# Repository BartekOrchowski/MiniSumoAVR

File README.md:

## MiniSumo Robot – ATmega328P 

This project is a MiniSumo robot developed during a workshop organized by the KoNaR student scientific association. It is based on the ATmega328P microcontroller and represents my first hands-on experience with designing, assembling, and programming a robot from scratch.

## Overview

The goal of the project was to create an autonomous MiniSumo robot that could:
- Detect and engage with an opponent using distance sensors
- Stay within the ring using line sensors
- Control DC motors for movement via an H-bridge

## Working Features

Despite the project being incomplete, several features were successfully implemented:
- ✅ **DC motor control** using an H-bridge
- ✅ **Distance measurement** from four VL53L0X sensors (basic functionality working)
- ✅ **ADC** for line sensor

## Issues and Challenges

Several hardware issues:
- ❌ Incorrect electrical connections
- ❌ Improper wiring of XSHUT pins for the VL53L0X distance sensors

Due to these problems, the robot was not fully operational, and the project was paused before final testing and competition.

## Future Plans

Although the current version of the robot is unfinished, I may return to this project in the future to redesign the PCB, correct the hardware issues, and complete the software stack.

---

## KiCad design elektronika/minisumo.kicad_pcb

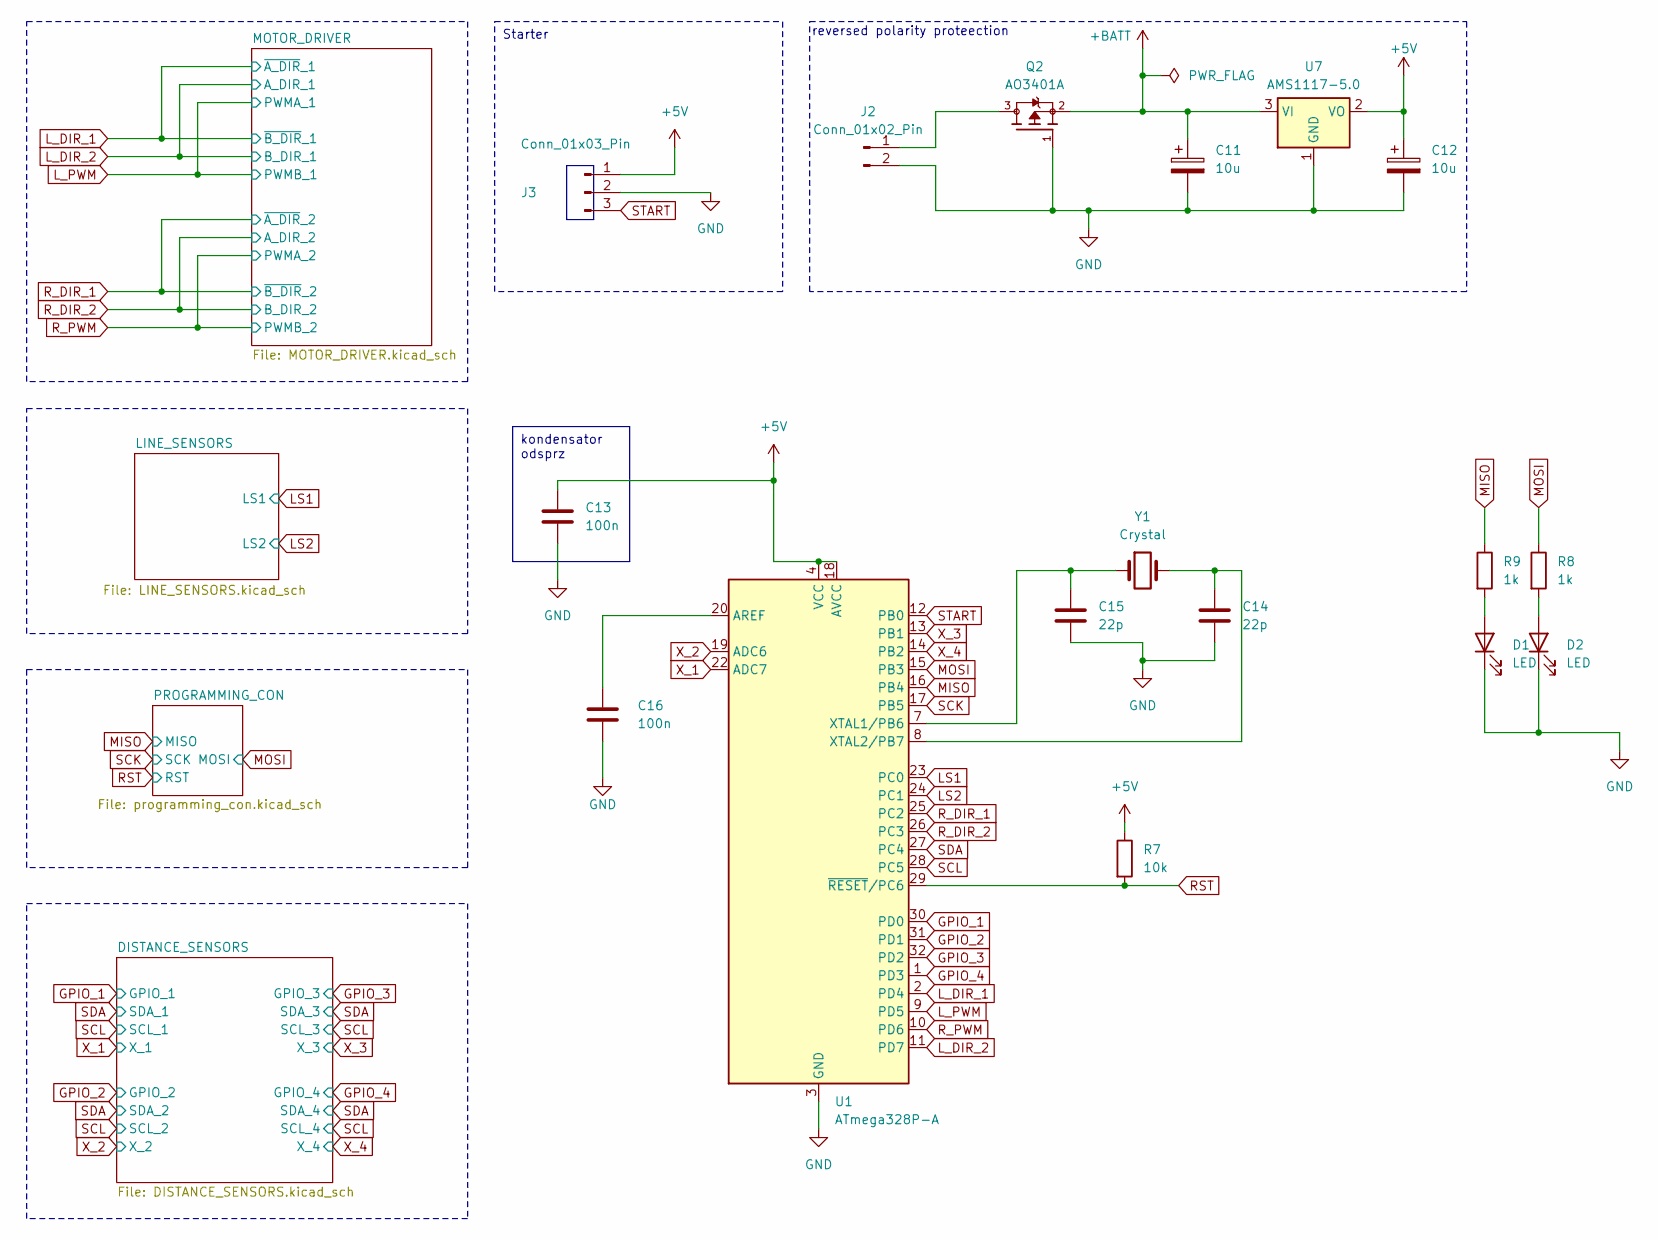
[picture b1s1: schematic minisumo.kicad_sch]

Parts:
C11, C12: 10u; CP_EIA-3528-21_Kemet-B_Pad1.50x2.35mm_HandSolder
C13, C16: 100n; LED_0805_2012Metric_Pad1.15x1.40mm_HandSolder
C14, C15: 22p; LED_0805_2012Metric_Pad1.15x1.40mm_HandSolder
D1, D2: LED; LED_0805_2012Metric_Pad1.15x1.40mm_HandSolder
J2: Conn_01x02_Pin; PinHeader_1x02_P2.54mm_Vertical
J3: Conn_01x03_Pin; PinHeader_1x03_P2.54mm_Vertical
Q2: AO3401A; SOT23-3; DigiKey_Part_Number 785-1001-2-ND
R7: 10k; R_0805_2012Metric_Pad1.20x1.40mm_HandSolder
R8, R9: 1k; R_0805_2012Metric_Pad1.20x1.40mm_HandSolder
U1: ATmega328P-A; TQFP-32_7x7mm_P0.8mm
U7: AMS1117-5.0; SOT-223-3_TabPin2
Y1: Crystal; Crystal_HC18-U_Vertical

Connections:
+5V: C12.1, C13.1, J3.1, R7.1, U1.4 (VCC), U1.6 (VCC), U1.18 (AVCC), U7.2 (VO); also elsewhere on the board
+BATT: C11.1, Q2.2, U7.3 (VI); also elsewhere on the board
GND: C11.2, C12.2, C13.2, C14.2, C15.2, C16.2, D1.1 (K), D2.1 (K), J2.2, J3.2, Q2.1, U1.3 (GND), U1.5 (GND), U1.21 (GND), U7.1 (GND); also elsewhere on the board
GPIO_1: U1.30 (PD0); also elsewhere on the board
GPIO_2: U1.31 (PD1); also elsewhere on the board
GPIO_3: U1.32 (PD2); also elsewhere on the board
GPIO_4: U1.1 (PD3); also elsewhere on the board
LS1: U1.23 (PC0); also elsewhere on the board
LS2: U1.24 (PC1); also elsewhere on the board
L_DIR_1: U1.2 (PD4); also elsewhere on the board
L_DIR_2: U1.11 (PD7); also elsewhere on the board
L_PWM: U1.9 (PD5); also elsewhere on the board
MISO: R9.1, U1.16 (PB4); also elsewhere on the board
MOSI: R8.1, U1.15 (PB3); also elsewhere on the board
unnamed: D1.2 (A), R9.2
unnamed: D2.2 (A), R8.2
unnamed: J2.1, Q2.3
unnamed: C16.1, U1.20 (AREF)
unnamed: C15.1, U1.7 (XTAL1/PB6), Y1.1
unnamed: C14.1, U1.8 (XTAL2/PB7), Y1.2
RST: R7.2, U1.29 (~RESET/PC6); also elsewhere on the board
R_DIR_1: U1.25 (PC2); also elsewhere on the board
R_DIR_2: U1.26 (PC3); also elsewhere on the board
R_PWM: U1.10 (PD6); also elsewhere on the board
SCK: U1.17 (PB5); also elsewhere on the board
SCL: U1.28 (PC5); also elsewhere on the board
SDA: U1.27 (PC4); also elsewhere on the board
START: J3.3, U1.12 (PB0)
X_1: U1.22 (ADC7); also elsewhere on the board
X_2: U1.19 (ADC6); also elsewhere on the board
X_3: U1.13 (PB1); also elsewhere on the board
X_4: U1.14 (PB2); also elsewhere on the board

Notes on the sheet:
kondensator odsprz
Starter
reversed polarity proteection

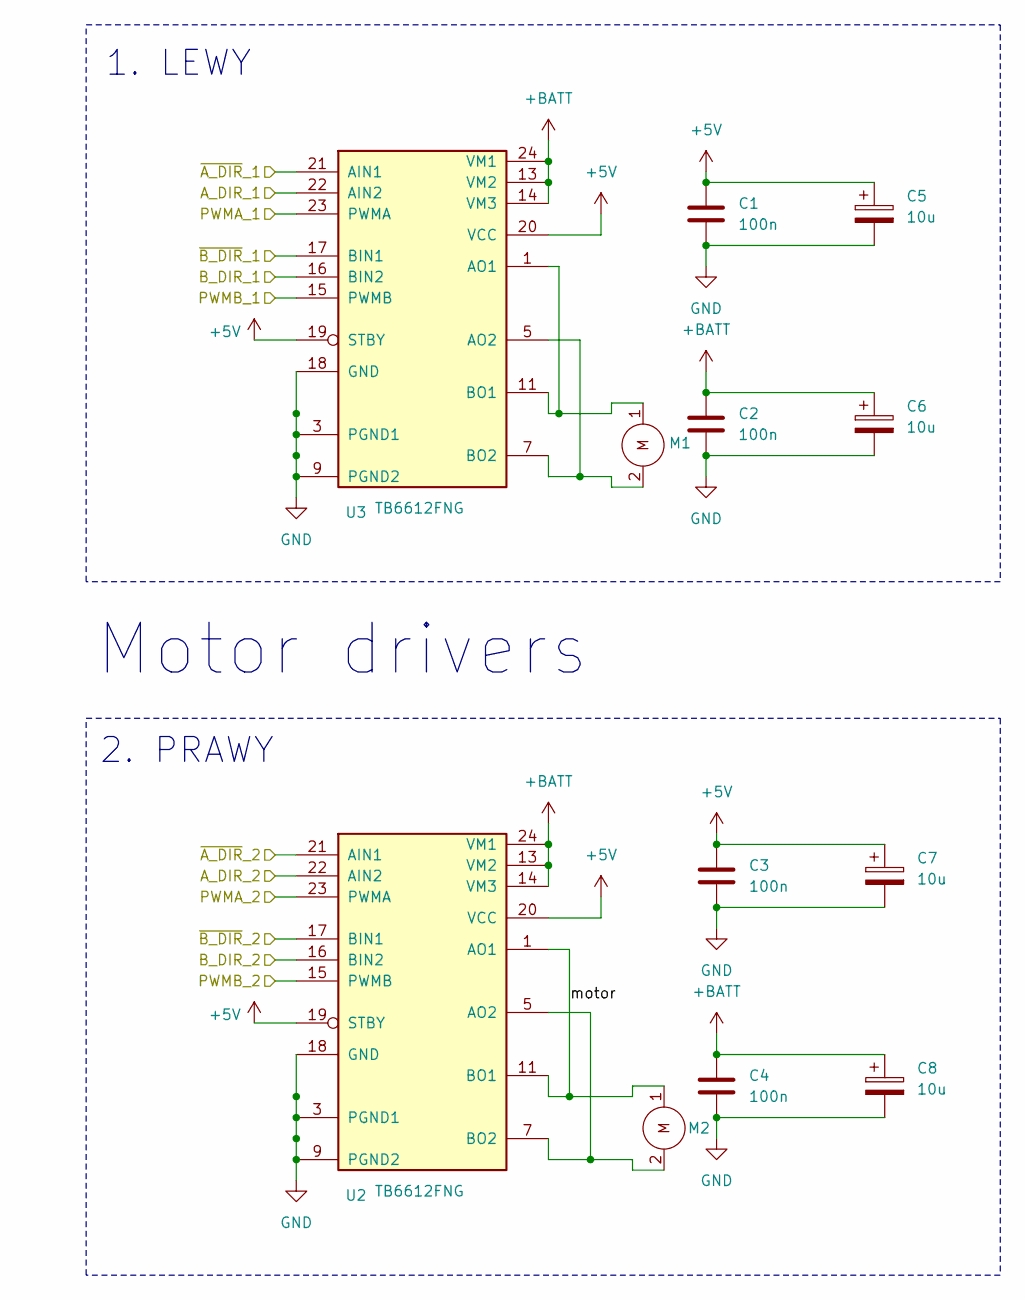
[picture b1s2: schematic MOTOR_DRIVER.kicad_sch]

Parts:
C1, C2, C3, C4: 100n; LED_0805_2012Metric_Pad1.15x1.40mm_HandSolder
C5, C6, C7, C8: 10u; CP_EIA-3528-21_Kemet-B_Pad1.50x2.35mm_HandSolder
M1, M2: Motor
U2, U3: TB6612FNG; SSOP-24_5.3x8.2mm_P0.65mm

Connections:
+5V: C1.1, C3.1, C5.1, C7.1, U2.19 (STBY), U2.20 (VCC), U3.19 (STBY), U3.20 (VCC); also elsewhere on the board
+BATT: C2.1, C4.1, C6.1, C8.1, U2.13 (VM2), U2.14 (VM3), U2.24 (VM1), U3.13 (VM2), U3.14 (VM3), U3.24 (VM1); also elsewhere on the board
/MOTOR_DRIVER/motor: M2.1, U2.1 (AO1), U2.2 (AO1), U2.11 (BO1), U2.12 (BO1)
GND: C1.2, C2.2, C3.2, C4.2, C5.2, C6.2, C7.2, C8.2, U2.3 (PGND1), U2.4 (PGND1), U2.9 (PGND2), U2.10 (PGND2), U2.18 (GND), U3.3 (PGND1), U3.4 (PGND1), U3.9 (PGND2), U3.10 (PGND2), U3.18 (GND); also elsewhere on the board
L_DIR_1: U3.17 (BIN1), U3.21 (AIN1); also elsewhere on the board
L_DIR_2: U3.16 (BIN2), U3.22 (AIN2); also elsewhere on the board
L_PWM: U3.15 (PWMB), U3.23 (PWMA); also elsewhere on the board
unnamed: M1.1, U3.1 (AO1), U3.2 (AO1), U3.11 (BO1), U3.12 (BO1)
unnamed: M1.2, U3.5 (AO2), U3.6 (AO2), U3.7 (BO2), U3.8 (BO2)
unnamed: M2.2, U2.5 (AO2), U2.6 (AO2), U2.7 (BO2), U2.8 (BO2)
R_DIR_1: U2.17 (BIN1), U2.21 (AIN1); also elsewhere on the board
R_DIR_2: U2.16 (BIN2), U2.22 (AIN2); also elsewhere on the board
R_PWM: U2.15 (PWMB), U2.23 (PWMA); also elsewhere on the board

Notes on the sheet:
1. LEWY
2. PRAWY
Motor drivers

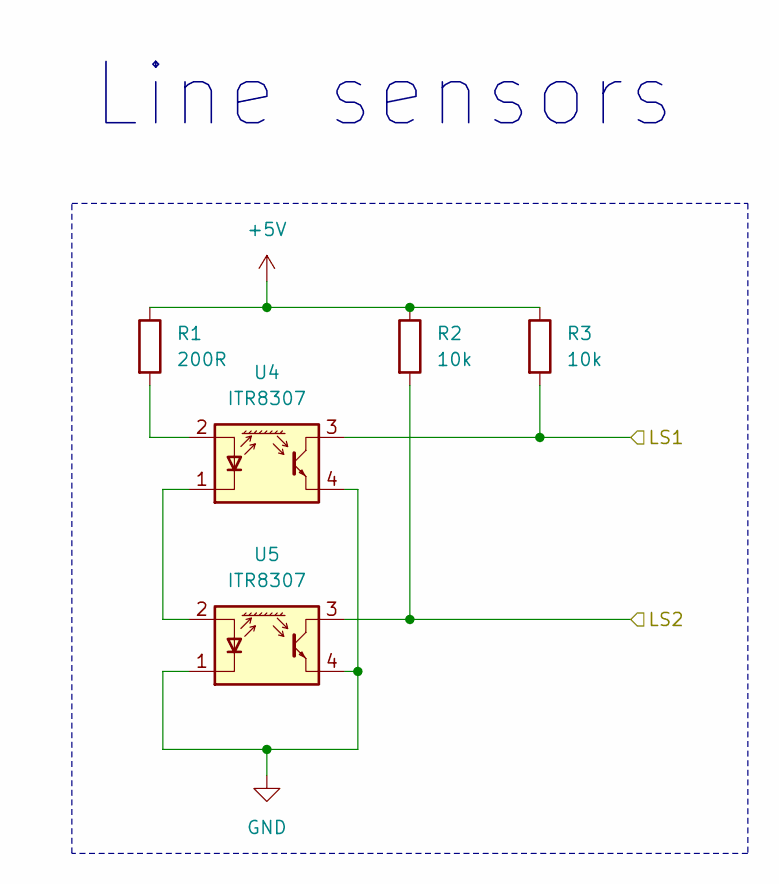
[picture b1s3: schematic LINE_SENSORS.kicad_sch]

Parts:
R1: 200R; R_0805_2012Metric_Pad1.20x1.40mm_HandSolder
R2, R3: 10k; R_0805_2012Metric_Pad1.20x1.40mm_HandSolder
U4, U5: ITR8307; Everlight_ITR1201SR10AR

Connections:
+5V: R1.1, R2.1, R3.1; also elsewhere on the board
GND: U4.4 (E), U5.1 (K), U5.4 (E); also elsewhere on the board
LS1: R3.2, U4.3 (C); also elsewhere on the board
LS2: R2.2, U5.3 (C); also elsewhere on the board
unnamed: R1.2, U4.2 (A)
unnamed: U4.1 (K), U5.2 (A)

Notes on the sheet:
Line sensors

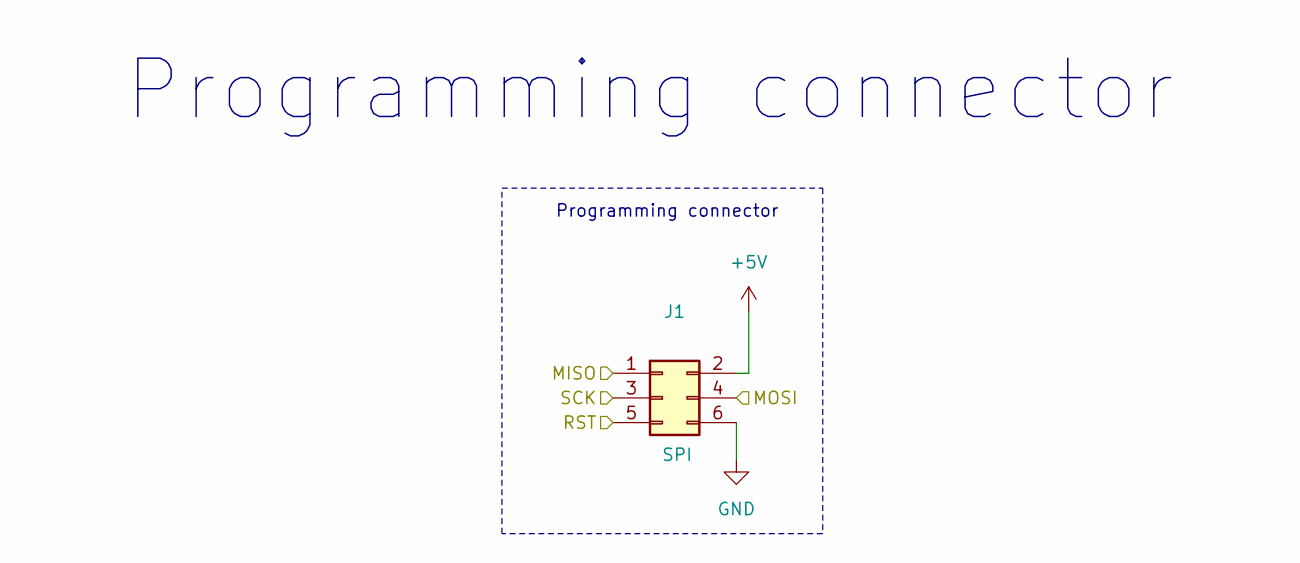
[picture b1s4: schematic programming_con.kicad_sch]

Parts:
J1: SPI; PinHeader_2x03_P2.54mm_Vertical

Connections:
+5V: J1.2; also elsewhere on the board
GND: J1.6; also elsewhere on the board
MISO: J1.1; also elsewhere on the board
MOSI: J1.4; also elsewhere on the board
RST: J1.5; also elsewhere on the board
SCK: J1.3; also elsewhere on the board

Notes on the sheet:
Programming connector

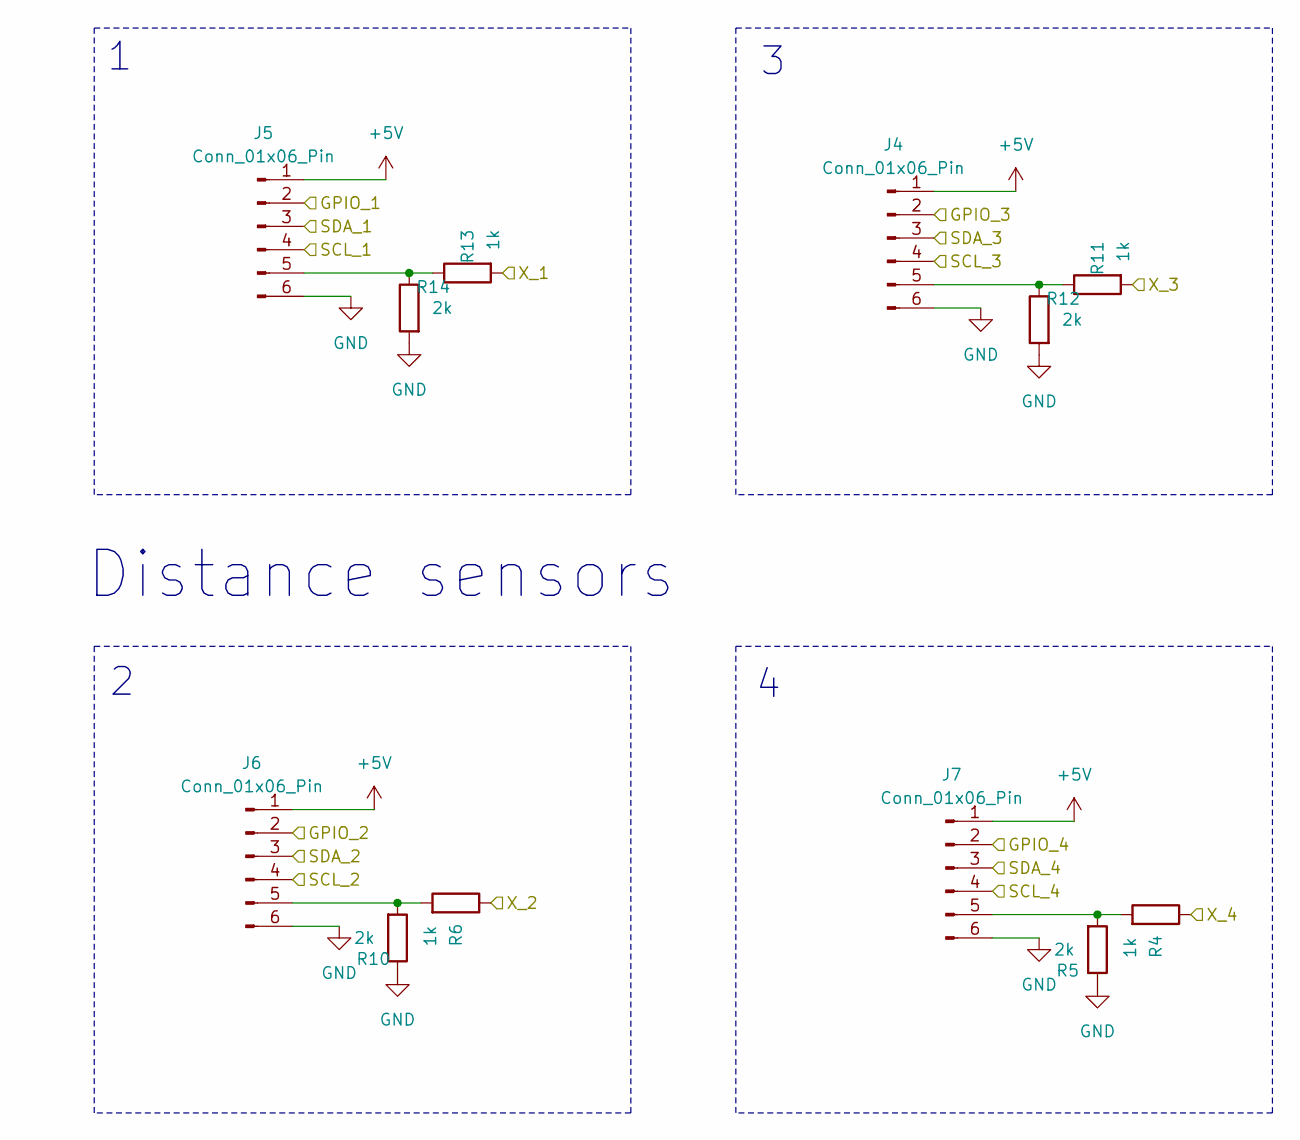
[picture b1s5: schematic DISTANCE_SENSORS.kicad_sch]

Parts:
J4, J5, J6, J7: Conn_01x06_Pin; PinHeader_1x06_P2.54mm_Vertical
R4, R6, R11, R13: 1k; R_0805_2012Metric_Pad1.20x1.40mm_HandSolder
R5, R10, R12, R14: 2k; R_0805_2012Metric_Pad1.20x1.40mm_HandSolder

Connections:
+5V: J4.1, J5.1, J6.1, J7.1; also elsewhere on the board
GND: J4.6, J5.6, J6.6, J7.6, R5.1, R10.1, R12.2, R14.2; also elsewhere on the board
GPIO_1: J5.2; also elsewhere on the board
GPIO_2: J6.2; also elsewhere on the board
GPIO_3: J4.2; also elsewhere on the board
GPIO_4: J7.2; also elsewhere on the board
unnamed: J4.5, R11.1, R12.1
unnamed: J5.5, R13.1, R14.1
unnamed: J6.5, R6.2, R10.2
unnamed: J7.5, R4.2, R5.2
SCL: J4.4, J5.4, J6.4, J7.4; also elsewhere on the board
SDA: J4.3, J5.3, J6.3, J7.3; also elsewhere on the board
X_1: R13.2; also elsewhere on the board
X_2: R6.1; also elsewhere on the board
X_3: R11.2; also elsewhere on the board
X_4: R4.1; also elsewhere on the board

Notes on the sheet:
Distance sensors

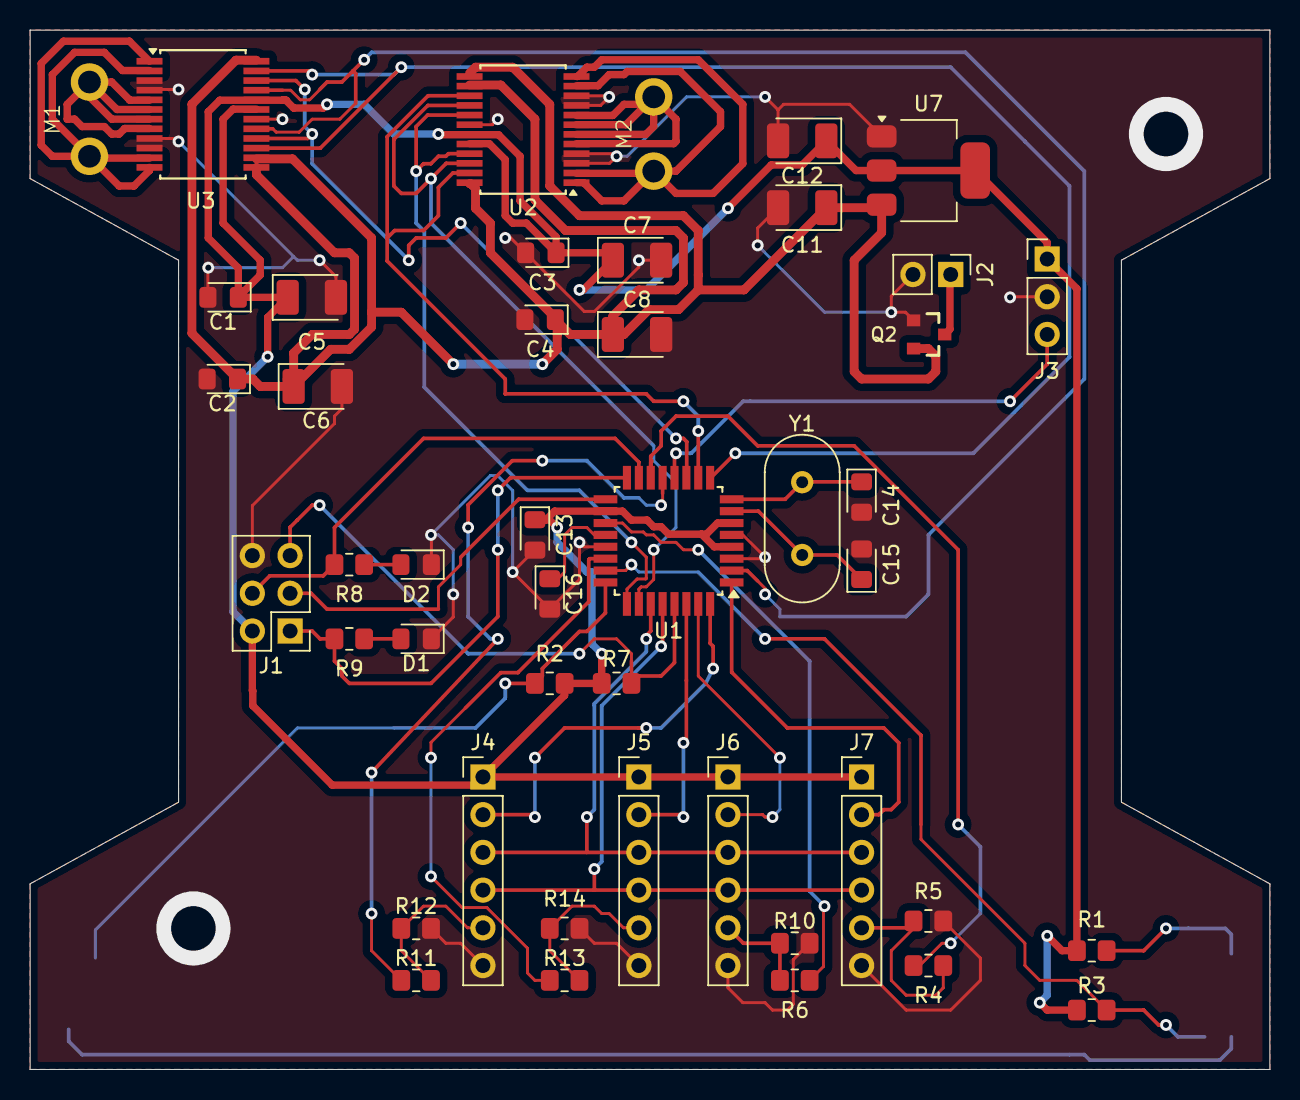
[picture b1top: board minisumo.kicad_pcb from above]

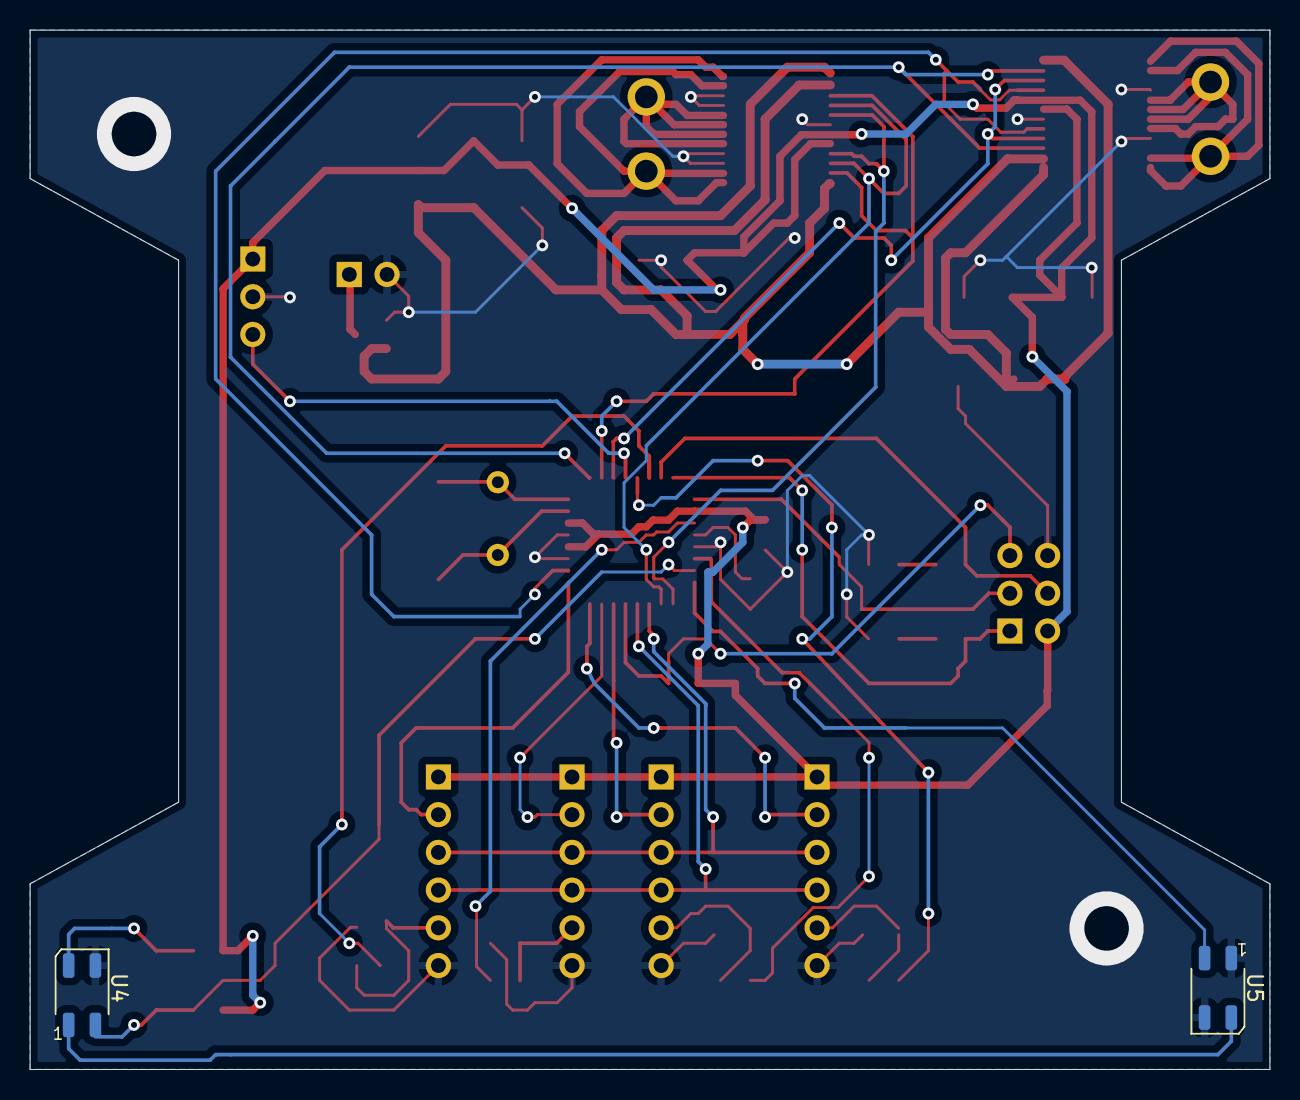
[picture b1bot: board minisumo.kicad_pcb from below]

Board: 2 copper layers, 83.5 x 70.0 mm, 47 parts (2 on the bottom side), 42 nets.

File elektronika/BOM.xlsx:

Reference | Value
C1, C2, C3, C4, C13, C16 | 100n
C5, C6, C7, C8, C11, C12 | 10u
C14, C15 | 22p
D1, D2 | LED
J1 | SPI
J2 | Conn_01x02_Pin
J3 | Conn_01x03_Pin
J4, J5, J6, J7 | Conn_01x06_Pin
M1, M2 | ~
Q2 | AO3401A
R1 | 200R
R2, R3, R7 | 10k
R4, R6, R8, R9, R11, R13 | 1k
R5, R10, R12, R14 | 2k
U1 | ATmega328P-A
U2, U3 | TB6612FNG
U4, U5 | ITR8307
U7 | AMS1117-5.0
Y1 | Crystal

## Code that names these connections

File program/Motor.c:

#include "Motor.h"

  //  Timer0  PWM PD6 (OC0A) i PD5 (OC0B)
  void Timer0_Init()
  {
	  //Fast PWM (WGM02 = 0, WGM01 = 1, WGM00 = 1)
	  TCCR0A |= (1 << WGM00) | (1 << WGM01);
	  TCCR0B |= (1 << CS01) | (1 << CS00);  // Prescaler 64

	  //PWM OC0A (PD6) i OC0B (PD5)
	  TCCR0A |= (1 << COM0A1) | (1 << COM0B1);

	  // turn off the motors
	  OCR0A = 0;
	  OCR0B = 0;

	  // output (PWM)
	  DDRD |= (1 << PD6) | (1 << PD5);
  }

  //pins for directions of both motors
  void Motor_Init()
  {
	  Timer0_Init();
	  // Ustawienie PC2, PC3 (lewy silnik) i PD4, PD7 (prawy silnik) jako wyjcia
	  DDRC |= (1 << PC2) | (1 << PC3);
	  DDRD |= (1 << PD4) | (1 << PD7);
  }

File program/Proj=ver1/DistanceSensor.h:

#pragma once

#include <stdint.h>
#include <avr/io.h>
#include <avr/delay.h>				

#include "vl53l0x.h"
#include "I2C.h"

void Timer1_Init(void); 

//Distance sensors
// XSHUT pins (dla czujników VL53L0X)
#define XSHUT_SENSOR1 PD0
#define XSHUT_SENSOR2 PD1				///////////////////////////////////connect x1 and x2 using jumper cables to pd0 and pd1
#define XSHUT_SENSOR3 PB1
#define XSHUT_SENSOR4 PB2

// I2C Addresses for sensors
#define SENSOR1_ADDR 0x30
#define SENSOR2_ADDR 0x31
#define SENSOR3_ADDR 0x32
#define SENSOR4_ADDR 0x33

void Xshut_Init(void);
void Xshut_Disable(uint8_t pin);
void Xshut_Enable(uint8_t pin);
void DistanceSensor_Init(void);
void DistanceSensor_SetAddr(uint8_t new_address);
uint16_t DistanceSensor_Read(uint8_t sensor_address);

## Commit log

2024-12-06 Start+LineSensor
2025-02-05 Added a big code update
2025-02-10 Motor Drivers
2025-02-28 PWM fight
2025-02-28 PWM fight2
2025-03-14 motor+line sensor
2025-03-17 Sensors
2025-03-18 Mechanika + dystans
2025-03-21 Final?
2025-06-06 fire problems
2025-06-10 Line sensors ADC
2026-03-09 Remove project attribution from README
